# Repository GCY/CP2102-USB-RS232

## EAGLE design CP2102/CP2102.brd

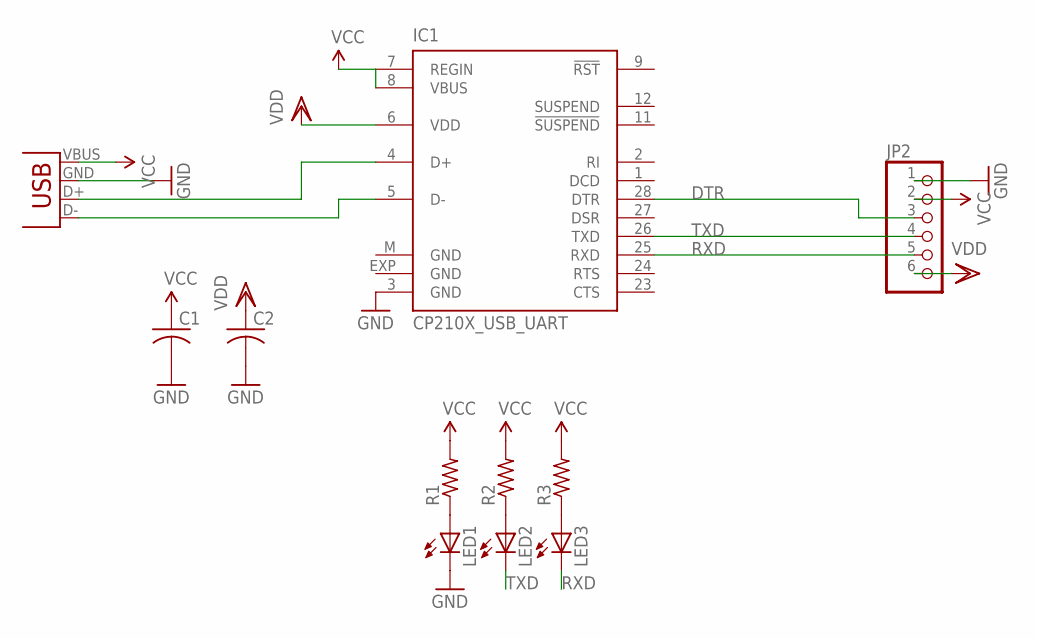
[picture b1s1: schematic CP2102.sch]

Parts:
C1, C2: C-USC1206; C1206
IC1: CP210X_USB_UART; MLP28
JP1: USB-A-H
JP2: PINHD-1X6; 1X06
LED1, LED2, LED3: LEDCHIPLED_0805; CHIPLED_0805
R1, R2, R3: R-US_M0805; M0805

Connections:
DTR: IC1.28 (DTR), JP2.3
GND: C1.2, C2.2, IC1.3 (GND), IC1.EXP (GND), IC1.M (GND), JP1.GND (VBUS), JP2.1, LED1.C
unnamed: LED3.A, R3.1
unnamed: LED2.A, R2.1
unnamed: LED1.A, R1.1
unnamed: IC1.4 (D+), JP1.D+ (D-)
unnamed: IC1.5 (D-), JP1.D- (D+)
RXD: IC1.25 (RXD), JP2.5, LED3.C
TXD: IC1.26 (TXD), JP2.4, LED2.C
VCC: C1.1, IC1.7 (REGIN), IC1.8 (VBUS), JP1.VBUS (GND), JP2.2, R1.2, R2.2, R3.2
VDD: C2.1, IC1.6 (VDD), JP2.6

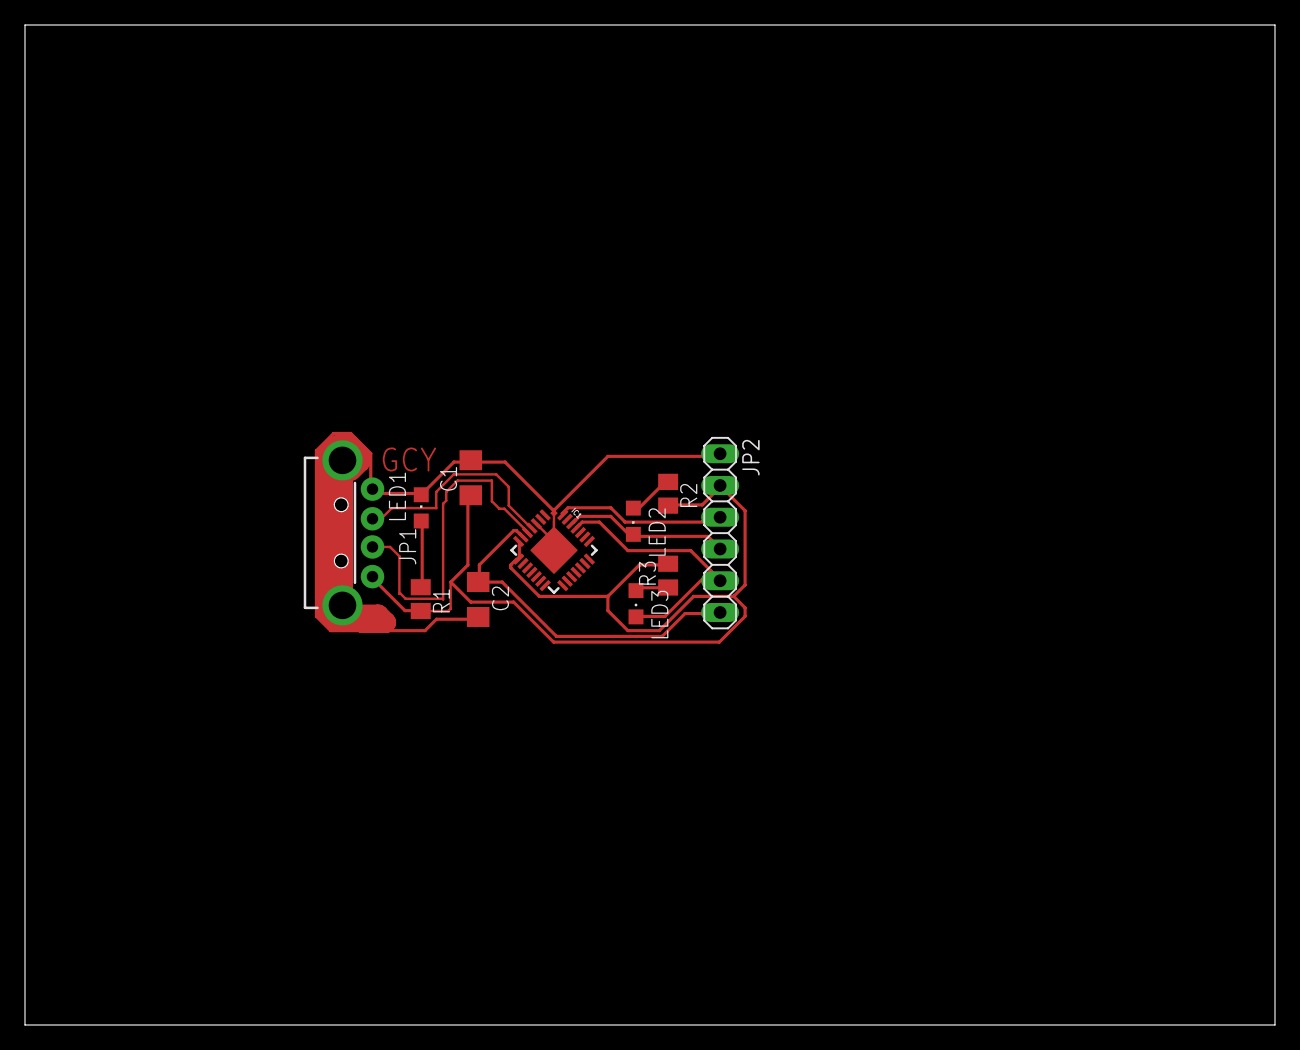
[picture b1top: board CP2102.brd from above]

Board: 2 copper layers, 100.0 x 80.0 mm, 11 parts (0 on the bottom side), 11 nets.

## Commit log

2016-02-02 v1.0

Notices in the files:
parts and their libraries:
SparkFun-DigitalIC: Licensing: CC v3.0 Share-Alike You are welcome to use this library for commercial purposes.
